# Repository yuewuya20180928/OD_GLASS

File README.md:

# OD_GLASS — ARS45 一体式智能眼镜

> **1 台样机** · ARS45 (12nm / 6 TOPS / 512MB) · MIPI-CSI 单路 sensor → NPU 跑 YOLOv5 INT8 80 类 → 800×600 显示 + JBD 走鹃Ⅱ + 衍射光波导一拖二双目
> 硬指标: **端到端 < 60ms** · **皮肤接触 ≤43°C** · **续航 ≥1h (按需触发)**

本仓库记录项目的**全部工程信息 + 4-Agent 协同开发体系**。
最新快照: `docs/PROJECT_STATUS.md` · 决策: `docs/DECISIONS.md` · 未闭环问题: `docs/OPEN_ISSUES.md`

---

## 0. ★ 从这里开始 → [`docs/START_HERE.md`](docs/START_HERE.md)

> 30 秒知道: 现在在哪个阶段 / 这一阶段要什么 / 正在跑什么 / 下一步 3 件事 / 哪些数字不能信

## 0. 这不是一个人的项目 —— 是 4 个 Agent 的协同产物

```
                      ┌─────────────────────────┐
                      │  main = 项目总工 (moli) │
                      │  方案/选型/拆解/计划/   │
                      │  收口/质量与进度把控     │
                      └───────────┬─────────────┘
        ┌─────────────────────────┼─────────────────────────┐
        │                         │                         │
┌───────▼────────┐      ┌─────────▼────────┐      ┌─────────▼────────┐
│  hw-lead       │      │  sw-lead         │      │  mech-lead      │
│  硬件总工      │      │  软件总工        │      │  结构总工(散热) │
│  原理图/PCB    │      │  需求拆解/方案   │      │  空间预算/散热  │
│  拆解/审核     │      │  开发与验证      │      │  打印件实现     │
└────────────────┘      └──────────────────┘      └──────────────────┘
        ↑                        ↑                        ↑
        └──────── 走共享状态源 STATE.yaml + HANDOFF 交接单 ────┘
              ★ 三个子总工之间【不做直接沟通】(星型拓扑, 硬规则)
```

**为什么这么设计**: 项目总工的核心职责是"需求对接 + 跨模块串联", 而它已经持有全部项目上下文; 另建一个总工等于把上下文切一半出去还多一跳中转。三个子总工之间**横向信息流走文件, 不走对话** —— 堵死的是"对话"不是"信息", 否则结构总工看不到硬件的 PCB 尺寸, 各写各的。

→ 完整说明: **[`docs/AGENT_SYSTEM.md`](docs/AGENT_SYSTEM.md)**

---

## 0.4 当前进展与待办 (一页看懂) → [`docs/STATUS_SUMMARY.md`](docs/STATUS_SUMMARY.md)
> 2026-10-26 19:45 更新: 一天内闭环 8 件 (打印包 Rev A / ISP 整幅 scale / 功耗 V2 / 电池容量口径 / 可靠性 / 原理图 V1 启动 / 网上查证 / 工程基建), 未闭环 41 条, 3 个硬指标的真实状态与杠杆, 待办分 5 桶, 风险 Top 3。

## 0.5 接下来干什么 → [`docs/TODO.md`](docs/TODO.md)

```
A 桶 立刻可派 (内部, 不等任何人)   14 条   → 三个总工的活, 随时能派
B 桶 等你拍板 (回一句就解锁)         3 条   → 3 份外发草稿 + 测试设备预算
C 桶 等外部 (原厂 9 / JBD 3)        13 条   → 不是谁的锅, 但有 due 与升级点
D 桶 依赖关系                              → 草稿发出 → G1; 打印环境 → G2; 测试设备 → G3
```

---

## 1. 当前状态 (自动生成, 数字与真源一致)

> ★**本 README 不含任何会过期的数字** —— 状态一律看下面这几份**自动生成**的文档:

| 文档 | 内容 |
|---|---|
| **[`docs/START_HERE.md`](docs/START_HERE.md)** | ★**接手指南: 30 秒现状 / 下一步 3 件事 / 正在跑 / 等你拍板 / 哪些数字不能信** |
| [`docs/STATUS_SUMMARY.md`](docs/STATUS_SUMMARY.md) | 一页看懂 (现状 / 闭环了什么 / 三个硬指标真状态 / 待办分桶 / 风险 Top3) |
| [`docs/PROJECT_STATUS.md`](docs/PROJECT_STATUS.md) | 8 节状态快照 (质量门 / 阶段门 / 就绪度 / 配置审计 / 决策账) |
| [`docs/OPEN_ISSUES.md`](docs/OPEN_ISSUES.md) | 问题清单 (按责任方分桶 + 未闭环明细 + 已关闭台账) |
| [`docs/TODO.md`](docs/TODO.md) | 接下来干什么 (在飞 / 可派 / 等你 / 等外部 / 依赖关系 / 复现命令) |

## 2. 目录

```
docs/
  TODO.md                 ★★ **接下来干什么** (按"能不能真动"分 4 桶: 立刻可派 / 等你拍板 / 等外部 / 依赖关系) —— 先看这份
  AGENT_SYSTEM.md          ★ 4 个 Agent 的职责/边界/配置/通信规则/质量门 (核心)
  PROJECT_STATUS.md          当前状态快照 (自动生成)
  DECISIONS.md               决策日志 (老板拍板原话 + 推导)
  OPEN_ISSUES.md             未闭环问题清单 (自动生成)
  FRAMEWORK_SCOPE.md         框架裁剪基线表 (9 域 68 项 + 6 项专属, 逐条裁剪)
  DECISION_TABLE_Q1_Q4_Q17.md  端到端/续航/帧率 三件决策表
  CERT_CHECKLIST.md          认证清单 (仅国内)
  STRESS_TEST_2026-10-25.md  Agent 通信压测报告 (抓到 11 个缺陷)
  INTERFACES.md              跨模块接口契约
  PRINT_SETUP.md             打印执行卡 (P2S 切片参数 + 41 项测量)
config/
  openclaw.agents.json     ★ 脱敏后的 4-Agent 配置 (凭据已剔除)
  agents/{main,hw-lead,sw-lead,mech-lead}/AGENTS.md
                           ★ 四个角色的岗位说明书 (职责/边界/交付标准)
projects/smart_glasses/    完整项目库 (真源)
  PROJECT_TRACKER.md         ★ 唯一真源 (35+ 条锁死变量 + 全部章节)
  state/                     状态源协议 + 11 个质量门/巡检脚本 (可复现)
  HW/ SW/ MECH/ REQ/ HANDOFF/ PRINT/  三个总工的产出区
  FRAMEWORK/                 ★ 框架层文档 (项目总工产出)
    ARCH_DIAGRAM.md            系统架构 / 信号流 / 数据流
    STACKUP.md                 尺寸堆叠 (镜脚/镜框/镜头)
    POWER_TREE.md              电源拓扑 + 热账 + 散热三件套
    INTERFACE_SPEC.md          ★ 接口规格书 (电气/机械/热/软件四层)
    RISK_REGISTER.md           ★ 风险登记册 (21 风险 + 应急备选 + 复查节奏)
    RTM.md                     ★ 需求→设计→验证 追溯矩阵
    CHANGE_LOG.md              ★ 规格变更追踪 (含 10 条已作废结论)
    EXTERNAL_PARTIES.md        ★ 外部方管理 (含"未回时的备份方案")
    QCP.md                     来料检验 + 整机测试项
    AFTERSALES.md              售后诊断 + 返修流程
    FRAMEWORK_SCOPE.md         9 域 68 项逐条裁剪基线
```

---

## 3. 怎么跑 (全部可复现, 不需要额外环境)

```bash
cd projects/smart_glasses

./status.sh                    # 一屏: 进展/待办(按责任方分 5 桶)/卡点/风险
python3 state/advance.py       # 下一批可执行动作 (--apply 落盘派活)
python3 state/issue_check.py   # 问题闭环门 (字段/状态机/验证分离/逾期/双向覆盖)
python3 state/stage_gate.py    # 阶段门: 现在在第几关, 缺什么
python3 state/readiness.py     # 执行就绪度 (组织与机制, 38 条判据)
python3 state/agent_config_check.py   # Agent 配置审计 (81 条判据, 能否开工)
python3 state/daily_check.py   # 每日巡检 + 漂移检测
python3 state/merge.py         # 状态源合并 (rc 0=完整 2=不完整 1=崩)
```

---

## 4. 三条最该记住的教训

**① 数字不能自己估** — 我给决策表写"0.23W → 皮肤 38-40°C ✅", 结构总工重算是 **46.5°C ❌ 仍超 43°C 红线**, 还漏了整个充电场景 (0.8W → 75.1°C)。
→ *给用户的数必须引子总工的核算原文。*

**② 验收分离: 自己修的必须别人验** — 问题的 `verify_by ≠ owner` 是硬门禁, 自己修自己验等于没验。三个子总工因此抓到总工的三处错 (温度数 / Q17 切换判据 / 验证人填自己)。

**③ 阶段性结论要标证据等级** — `[实测] / [官方] / [推算] / [0数据]`。本项目**至今零实测**, 所有数字都是推算; 推算值不能冒充实测, 阶段门只认 `kind == "实测"`。

---

## 5. 现状一句话

> **纸面阶段已做到滴水不漏, 但一个实测数都没有。**
> 阶段门 G0 → G1 (原理图/PCB 定稿) 差 4 项; 三个硬指标 (端到端 60ms / 皮肤 43°C / 续航 1h) 目前**全是推算**,
> 达标结论必须等投板后的实测。
> → **当前目标 / 计划 / 下一步 / 正在跑 / 等你拍板: 见 [`docs/START_HERE.md`](docs/START_HERE.md)** (自动生成, 数字不过期)
> → **唯一真源**: `projects/smart_glasses/PROJECT_TRACKER.md` (有章节地图)

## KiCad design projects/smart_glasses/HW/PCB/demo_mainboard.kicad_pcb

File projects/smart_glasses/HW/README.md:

# HW/ — 硬件总工 hw-lead 的产出区

规则:
- 只放**本角色**的交付物, 文件名带日期/版本 (例: `2025-10-25_schematic_v1.pdf`)
- 大文件 (PDF / PCB / 3D / 固件) 放这里, 聊天里只发绝对路径
- 需求变更先写交接单到 `../HANDOFF/`, 不要直接改 `../PROJECT_TRACKER.md`

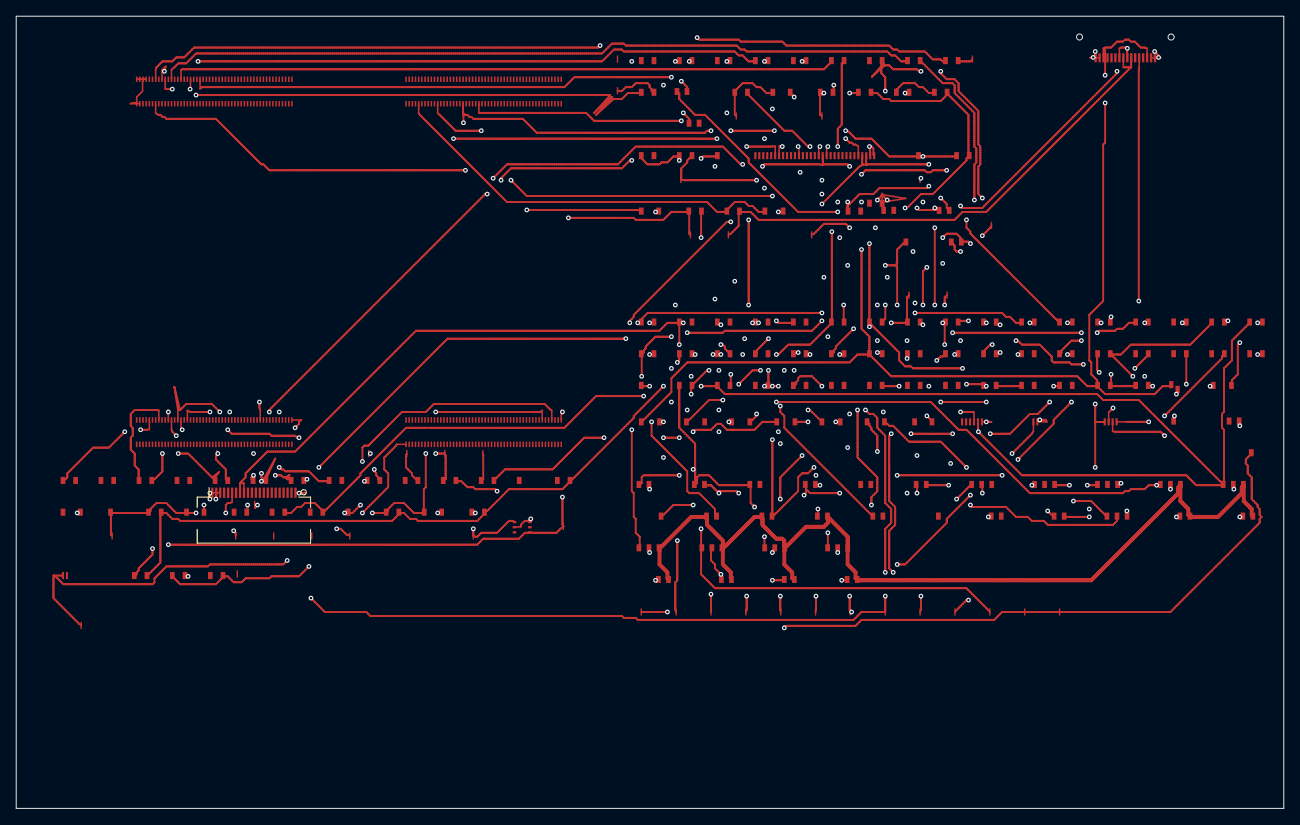
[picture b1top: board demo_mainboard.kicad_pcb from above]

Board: 8 copper layers, 160.0 x 100.0 mm, 186 parts (0 on the bottom side), 115 nets.

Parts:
BT_432243: 432243 3.7V ≥420mAh
CHG_GND_STAR: 单点汇流位
CONN_CAM: GND
CONN_LIGHT: HIROSE FH12-22S-0.5SH(55) 22p 0.5mm
C_AC_CSI_D0_CK_N, C_AC_CSI_D0_CK_P, C_AC_CSI_D0_D0_N, C_AC_CSI_D0_D0_P, C_AC_CSI_D0_D1_N, C_AC_CSI_D0_D1_P, C_AC_CSI_D0_D2_N, C_AC_CSI_D0_D2_P, C_AC_CSI_D0_D3_N, C_AC_CSI_D0_D3_P: 100nF ±10%
C_BULK_LIGHT_1V8, C_BULK_LIGHT_3V3: 10µF
C_BULK_SENSOR_AVDD: 10µF
C_BULK_SENSOR_CORE: 10µF
C_BULK_SENSOR_VDD_IO: 10µF
C_BULK_VDD_1V8_IO, C_BULK_VDD_3V3_IO: 10µF
C_BULK_V_CORE: 10µF
C_BULK_V_SOC_IO: 10µF
C_DET_BAT: 100nF ±10%
C_DET_VBUS_D: 100nF ±10%
C_HF_LIGHT_1V8, C_HF_LIGHT_3V3: 100nF
C_HF_SENSOR_AVDD: 100nF
C_HF_SENSOR_CORE: 100nF
C_HF_SENSOR_VDD_IO: 100nF
C_HF_VDD_1V8_IO, C_HF_VDD_3V3_IO: 100nF
C_HF_V_CORE: 100nF
C_HF_V_SOC_IO: 100nF
C_KEY_CAM: 100nF ±10%
C_KEY_PWR: 100nF ±10%
C_KEY_VM: 100nF ±10%
C_KEY_VP: 100nF ±10%
C_RST: 100nF ±10%
C_SUPV: 100nF ±10%
C_SW_IN: 10µF ±20%
C_SW_OUT: 10µF ±20%
C_TEMP: 100nF ±10%
C_VBUS_DEMO: 10µF ±20%
C_VBUS_GND: [待选型] 100µF
C_XTAL_IN: 12pF ±10%
C_XTAL_OUT: 12pF ±10%
D_ESD_CAM: ESD 阵列 [待选型]
D_ESD_DEMO: ESD 阵列 [待选型] (USB 2.0)
D_ESD_LIGHT: ESD 阵列 [待选型]
D_ESD_USB_D: ESD 阵列 [待选型] (USB 2.0 双通道)
D_LED_B: LED (待选型)
D_LED_G: LED (待选型)
D_LED_R: LED (待选型)
FB_DEMO: π 滤波磁珠 [待选型]
J_BOOT1: 启动存储焊盘位 (4p 信号 + 2p 电源/GND 预留)
J_CHG: SoM BTB CHG (100pin, 部分已分配)
J_DEBUG: 1×4 1.27mm 排针 (JTAG)
J_SOM_P1: Hirose DF40C-100DS-0.4V(51) 100pin 0.4mm (SOM P1)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
J_SOM_P2: Hirose DF40C-100DS-0.4V(51) 100pin 0.4mm (SOM P2)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
J_SOM_P3: Hirose DF40C-100DS-0.4V(51) 100pin 0.4mm (SOM P3)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
J_SOM_P4: Hirose DF40C-100DS-0.4V(51) 100pin 0.4mm (SOM P4)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
J_UART: 1×2 1.27mm 排针 (UART)
J_USB_C: GCT USB4105-16P USB-C 电源口 (自绘, 原厂图纸 Rev B3)
Q1, Q2: [待选型] N-MOS
Q_AND: [待选型] N-MOS (硬件 AND)
Q_ENVC: [待选型] N-MOS (反相)
Q_PG: [待选型] **P-MOS 高边开关** (低漏, Vgs(th) 明确)
R_BAT_DET_1, R_BAT_DET_2: 1M ±1%
R_CC1_D: 5.1k ±1% (CC1 下拉)
R_CC2_D: 5.1k ±1% (CC2 下拉)
R_EN_VCORE: 10k ±1%
R_ID_JMP0, R_ID_JMP1: 0Ω (跳线位)
R_JTAG_TCK: 100Ω ±1%
R_JTAG_TDI: 100Ω ±1%
R_JTAG_TDO: 100Ω ±1%
R_JTAG_TMS: 100Ω ±1%
R_KEY_CAM: 10k ±1%
R_KEY_PWR: 10k ±1%
R_KEY_VM: 10k ±1%
R_KEY_VP: 10k ±1%
R_LED_B: 1k ±1%
R_LED_G: 1k ±1%
R_LED_R: 1k ±1%
R_NTC_BAT: 103AT NTC ±1% (贴电芯, 另一端接 TS 专用回流)
R_PD_ON: 10k ±1%
R_PG_PULL: 10k ±1%
R_PU_BOOT_N: 10k ±1%
R_PU_I2CA_SCL, R_PU_I2CA_SDA: 2.2k ±1%
R_PU_I2CB_SCL, R_PU_I2CB_SDA: 4.7k ±1%
R_PU_ID0, R_PU_ID1: 10k ±1%
R_PU_PG: 10k ±1%
R_PU_RESET_N: 10k ±1%
R_SEL_CK_N: 0Ω
R_SEL_CK_P: 0Ω
R_SEL_D0_N, R_SEL_D0_P, R_SEL_D1_N, R_SEL_D1_P, R_SEL_D2_N, R_SEL_D2_P, R_SEL_D3_N, R_SEL_D3_P: 0Ω
R_SER_CSI_MCLK: [待原厂]
R_SER_FSIN: 50Ω ±1%
R_SER_RESET_N: 1k ±1%
R_SER_SPI_CSn: 0Ω (串阻位)
R_SER_SPI_MISO: 0Ω (串阻位)
R_SER_SPI_MOSI: 0Ω (串阻位)
R_SER_SPI_SCLK: 0Ω (串阻位)
R_SER_USB_D_N: 22Ω ±1%
R_SER_USB_D_P: 22Ω ±1%
R_SUPV_DIV1: [待选型] 分压上臂 (0Ω 跳线位)
R_SUPV_DIV2: [待选型] 分压下臂 (0Ω 跳线位)
R_TS_PULL: 30.31k ±1%
R_VBUS_DET_D1: 1M ±1% (上臂)
R_VBUS_DET_D2: 1M ±1% (下臂)
SW_BOOT: BOOT 按键 (待选型)
SW_KEY_CAM: 按键 (待选型)
SW_KEY_PWR: 按键 (待选型)
SW_KEY_VM: 按键 (待选型)
SW_KEY_VP: 按键 (待选型)
SW_RST: 复位按键 (待选型)
TP_BAT: 测试点
TP_BAT_CHG: 跨铰链段压降测点
TP_BOOT: 测试点
TP_CSI_CK_N: 测试点
TP_CSI_CK_P: 测试点
TP_CSI_D0_N, TP_CSI_D0_P: 测试点
TP_DSI_CK_N: 测试点
TP_DSI_CK_P: 测试点
TP_DSI_D0_N, TP_DSI_D0_P, TP_DSI_D1_N, TP_DSI_D1_P, TP_DSI_D2_N, TP_DSI_D2_P, TP_DSI_D3_N, TP_DSI_D3_P: 测试点
TP_FSIN: 测试点
TP_I2CA_SCL, TP_I2CA_SDA, TP_I2CB_SCL, TP_I2CB_SDA: 测试点
TP_ID: 测试点
TP_JTAG: 测试点
TP_KEY_PWR: 测试点
TP_KEY_VM: 测试点
TP_KEY_VP: 测试点
TP_LED_B: 测试点
TP_LED_G: 测试点
TP_LED_R: 测试点
TP_LIGHT_3V3: 测试点
TP_MCLK: 测试点
TP_PG: 测试点
TP_PG_VCORE: PG (开漏, 需上拉)
TP_PG_VIO: PG (开漏, 需上拉)
TP_RESET: 测试点
TP_SYS: 测试点
TP_UART: 测试点
TP_USB_D_N: 测试点
TP_USB_D_P: 测试点
TP_VCORE: 测试点
TP_VIO: 测试点
U_BATPROT: BQ2970
U_DCDC_VCORE: EN 输入 (高 = 使能)
U_DCDC_VIO: EN 输入 (高 = 使能)
U_EN_SW: EN 输入 (高=放行底板)
U_LDO_IO18, U_LDO_IO33: EN (pin3)
U_LDO_L18, U_LDO_L33: EN (pin3)
U_LDO_S12, U_LDO_S18B: EN (pin3)
U_LDO_S28: GND (pin2)
U_PWR_SW: VIN (输入)
U_SUPV: CT 脚 (阈值/延时选择)
U_TEMP: TI TMP117 (WSON-6 DRV0006B, 2x2mm)
X1: 晶振焊盘位 (不装)

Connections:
BAT: R_BAT_DET_1.2, TP_BAT.1, U_BATPROT.4
BAT_CELL_N: BT_432243.2, U_BATPROT.6
BAT_CELL_P: BT_432243.1, Q1.3
BAT_CHG: J_CHG.1, TP_BAT_CHG.1
BAT_COUT: Q2.5, U_BATPROT.2
BAT_DET: C_DET_BAT.1, J_SOM_P1.38, R_BAT_DET_1.1, R_BAT_DET_2.1
BAT_DOUT: Q1.5, U_BATPROT.3
BAT_GATE: Q1.2, Q2.2
BAT_PROT_CELL: Q1.4, Q2.3
BAT_PROT_CELL2: Q2.4, U_BATPROT.5
BAT_SW: C_SW_IN.1, Q_PG.2, U_BATPROT.7, U_PWR_SW.1
BOOT_N: J_SOM_P1.28, R_PU_BOOT_N.1, SW_BOOT.1, TP_BOOT.1
CAM_RESET_N: CONN_CAM.27, J_SOM_P1.54
CARRIER_BOARD_EN: J_SOM_P3.87, U_EN_SW.2
CSI_D0_CK_N: CONN_CAM.17, C_AC_CSI_D0_CK_N.2, TP_CSI_CK_N.1
CSI_D0_CK_N_SRC: C_AC_CSI_D0_CK_N.1, J_SOM_P4.77
CSI_D0_CK_P: CONN_CAM.18, C_AC_CSI_D0_CK_P.2, D_ESD_CAM.2, TP_CSI_CK_P.1
CSI_D0_CK_P_SRC: C_AC_CSI_D0_CK_P.1, J_SOM_P4.79
CSI_D0_D0_N: CONN_CAM.14, C_AC_CSI_D0_D0_N.2, TP_CSI_D0_N.1
CSI_D0_D0_N_SRC: C_AC_CSI_D0_D0_N.1, J_SOM_P4.65
CSI_D0_D0_P: CONN_CAM.15, C_AC_CSI_D0_D0_P.2, TP_CSI_D0_P.1
CSI_D0_D0_P_SRC: C_AC_CSI_D0_D0_P.1, J_SOM_P4.67
CSI_D0_D1_N: CONN_CAM.11, C_AC_CSI_D0_D1_N.2
CSI_D0_D1_N_SRC: C_AC_CSI_D0_D1_N.1, J_SOM_P4.71
CSI_D0_D1_P: CONN_CAM.12, C_AC_CSI_D0_D1_P.2
CSI_D0_D1_P_SRC: C_AC_CSI_D0_D1_P.1, J_SOM_P4.73
CSI_D0_D2_N: CONN_CAM.5, C_AC_CSI_D0_D2_N.2
CSI_D0_D2_N_SRC: C_AC_CSI_D0_D2_N.1, J_SOM_P4.83
CSI_D0_D2_P: CONN_CAM.6, C_AC_CSI_D0_D2_P.2
CSI_D0_D2_P_SRC: C_AC_CSI_D0_D2_P.1, J_SOM_P4.85
CSI_D0_D3_N: CONN_CAM.2, C_AC_CSI_D0_D3_N.2
CSI_D0_D3_N_SRC: C_AC_CSI_D0_D3_N.1, J_SOM_P4.89
CSI_D0_D3_P: CONN_CAM.3, C_AC_CSI_D0_D3_P.2
CSI_D0_D3_P_SRC: C_AC_CSI_D0_D3_P.1, J_SOM_P4.91
CSI_MCLK: CONN_CAM.20, R_SER_CSI_MCLK.2, TP_MCLK.1
CSI_MCLK_SRC: J_SOM_P2.45, R_SER_CSI_MCLK.1
DSI_D0_CK_N: CONN_LIGHT.5, R_SEL_CK_N.2, TP_DSI_CK_N.1
DSI_D0_CK_N_SRC: J_SOM_P3.69, R_SEL_CK_N.1
DSI_D0_CK_P: CONN_LIGHT.6, R_SEL_CK_P.2, TP_DSI_CK_P.1
DSI_D0_CK_P_SRC: J_SOM_P3.71, R_SEL_CK_P.1
DSI_D0_D0_N: CONN_LIGHT.8, R_SEL_D0_N.2, TP_DSI_D0_N.1
DSI_D0_D0_N_SRC: J_SOM_P3.57, R_SEL_D0_N.1
DSI_D0_D0_P: CONN_LIGHT.9, R_SEL_D0_P.2, TP_DSI_D0_P.1
DSI_D0_D0_P_SRC: J_SOM_P3.59, R_SEL_D0_P.1
DSI_D0_D1_N: CONN_LIGHT.2, R_SEL_D1_N.2, TP_DSI_D1_N.1
DSI_D0_D1_N_SRC: J_SOM_P3.63, R_SEL_D1_N.1
DSI_D0_D1_P: CONN_LIGHT.3, R_SEL_D1_P.2, TP_DSI_D1_P.1
DSI_D0_D1_P_SRC: J_SOM_P3.65, R_SEL_D1_P.1
DSI_D0_D2_N: CONN_LIGHT.16, R_SEL_D2_N.2, TP_DSI_D2_N.1
DSI_D0_D2_N_SRC: J_SOM_P3.75, R_SEL_D2_N.1
DSI_D0_D2_P: CONN_LIGHT.17, R_SEL_D2_P.2, TP_DSI_D2_P.1
DSI_D0_D2_P_SRC: J_SOM_P3.77, R_SEL_D2_P.1
DSI_D0_D3_N: CONN_LIGHT.18, R_SEL_D3_N.2, TP_DSI_D3_N.1
DSI_D0_D3_N_SRC: J_SOM_P3.81, R_SEL_D3_N.1
DSI_D0_D3_P: CONN_LIGHT.19, R_SEL_D3_P.2, TP_DSI_D3_P.1
DSI_D0_D3_P_SRC: J_SOM_P3.83, R_SEL_D3_P.1
EN_VCORE: Q_ENVC.3, R_EN_VCORE.1, U_DCDC_VCORE.13
FSIN_OUT: R_SER_FSIN.1, TP_FSIN.1
GND: CHG_GND_STAR.1, CONN_CAM.1, CONN_CAM.4, CONN_CAM.7, CONN_CAM.10, CONN_CAM.13, CONN_CAM.16, CONN_CAM.19, CONN_CAM.21, CONN_LIGHT.1, CONN_LIGHT.4, CONN_LIGHT.7, CONN_LIGHT.10, CONN_LIGHT.13, CONN_LIGHT.20, CONN_LIGHT.21, CONN_LIGHT.22, C_BULK_LIGHT_1V8.2, C_BULK_LIGHT_3V3.2, C_BULK_SENSOR_AVDD.2, C_BULK_SENSOR_CORE.2, C_BULK_SENSOR_VDD_IO.2, C_BULK_VDD_1V8_IO.2, C_BULK_VDD_3V3_IO.2, C_BULK_V_CORE.2, C_BULK_V_SOC_IO.2, C_DET_BAT.2, C_DET_VBUS_D.1, C_HF_LIGHT_1V8.2, C_HF_LIGHT_3V3.2, C_HF_SENSOR_AVDD.2, C_HF_SENSOR_CORE.2, C_HF_SENSOR_VDD_IO.2, C_HF_VDD_1V8_IO.2, C_HF_VDD_3V3_IO.2, C_HF_V_CORE.2, C_HF_V_SOC_IO.2, C_RST.2, C_SUPV.2, C_SW_IN.2, C_SW_OUT.2, C_TEMP.2, C_VBUS_DEMO.2, C_VBUS_GND.1, C_XTAL_IN.2, C_XTAL_OUT.2, D_ESD_CAM.1, D_ESD_DEMO.2, D_ESD_LIGHT.2, D_ESD_USB_D.2, D_LED_B.2, D_LED_G.2, D_LED_R.2, FB_DEMO.2, J_BOOT1.6, J_USB_C.A1, J_USB_C.A12, J_USB_C.B1, J_USB_C.B12, Q1.6, Q2.6, Q_AND.2, Q_ENVC.2, R_CC1_D.1, R_CC2_D.2, R_ID_JMP0.2, R_ID_JMP1.2, R_PD_ON.2, R_SUPV_DIV2.2, R_VBUS_DET_D2.2, SW_BOOT.2, SW_KEY_CAM.2, SW_KEY_PWR.2, SW_KEY_VM.2, SW_KEY_VP.2, SW_RST.2, U_EN_SW.4, U_LDO_IO18.2, U_LDO_IO18.5, U_LDO_IO33.2, U_LDO_IO33.5, U_LDO_L18.2, U_LDO_L18.5, U_LDO_L33.2, U_LDO_L33.5, U_LDO_S12.2, U_LDO_S12.5, U_LDO_S18B.2, U_LDO_S18B.5, U_LDO_S28.2, U_LDO_S28.5, U_PWR_SW.4, U_TEMP.2, U_TEMP.4
I2C_A_SCL: CONN_CAM.24, J_SOM_P2.31, R_PU_I2CA_SCL.1, TP_I2CA_SCL.1
I2C_A_SDA: CONN_CAM.25, J_SOM_P2.33, R_PU_I2CA_SDA.1, TP_I2CA_SDA.1
I2C_B_SCL: CONN_LIGHT.11, J_SOM_P2.11, R_PU_I2CB_SCL.1, TP_I2CB_SCL.1, U_TEMP.1
I2C_B_SDA: CONN_LIGHT.12, J_SOM_P2.1, R_PU_I2CB_SDA.1, TP_I2CB_SDA.1, U_TEMP.6
ID_DETECT_0: J_SOM_P1.32, R_ID_JMP0.1, R_PU_ID0.1, TP_ID.1
ID_DETECT_1: J_SOM_P1.36, R_ID_JMP1.1, R_PU_ID1.1
JTAG_TCK: J_DEBUG.1, R_JTAG_TCK.2, TP_JTAG.1
JTAG_TDI: J_DEBUG.3, R_JTAG_TDI.2
JTAG_TDO: J_DEBUG.4, R_JTAG_TDO.2
JTAG_TMS: J_DEBUG.2, R_JTAG_TMS.2
KEY_CAM: C_KEY_CAM.1, J_SOM_P4.3, R_KEY_CAM.1, SW_KEY_CAM.1
KEY_PWR: C_KEY_PWR.1, J_SOM_P1.64, R_KEY_PWR.1, SW_KEY_PWR.1, TP_KEY_PWR.1
KEY_VOL_M: C_KEY_VM.1, J_SOM_P4.1, R_KEY_VM.1, SW_KEY_VM.1, TP_KEY_VM.1
KEY_VOL_P: C_KEY_VP.1, J_SOM_P2.13, R_KEY_VP.1, SW_KEY_VP.1, TP_KEY_VP.1
LED_B: J_SOM_P4.21, R_LED_B.1, TP_LED_B.1
LED_B_D: D_LED_B.1, R_LED_B.2
LED_G: J_SOM_P4.19, R_LED_G.1, TP_LED_G.1
LED_G_D: D_LED_G.1, R_LED_G.2
LED_R: J_SOM_P1.80, R_LED_R.1, TP_LED_R.1
LED_R_D: D_LED_R.1, R_LED_R.2
LIGHT_1V8: C_BULK_LIGHT_1V8.1, C_HF_LIGHT_1V8.1, U_LDO_L18.1
LIGHT_3V3: CONN_CAM.28, CONN_CAM.29, CONN_LIGHT.14, CONN_LIGHT.15, C_BULK_LIGHT_3V3.1, C_HF_LIGHT_3V3.1, TP_LIGHT_3V3.1, U_LDO_L33.1
LIGHT_5V: CONN_CAM.30, CONN_CAM.31, D_ESD_LIGHT.1
NET_USB_D_N_TYPEC: J_USB_C.A7, J_USB_C.B7, R_SER_USB_D_N.2, TP_USB_D_N.1
NET_USB_D_P_TYPEC: J_USB_C.A6, J_USB_C.B6, R_SER_USB_D_P.2, TP_USB_D_P.1
PG_AND: Q_AND.3, Q_ENVC.1, R_PG_PULL.1, TP_PG_VCORE.1, TP_PG_VIO.1, U_DCDC_VCORE.4, U_DCDC_VIO.4
PWR_GOOD: J_CHG.6, Q_PG.3, R_PU_PG.2, TP_PG.1
PWR_ON: J_SOM_P3.88, Q_PG.1, R_PD_ON.1, U_PWR_SW.2
RAIL_DEMO_5V: C_VBUS_DEMO.1, D_ESD_DEMO.1, FB_DEMO.1, J_USB_C.A4, J_USB_C.A9, J_USB_C.B4, J_USB_C.B9, R_VBUS_DET_D1.1, U_EN_SW.1
RAIL_SOM_DCIN: J_SOM_P3.91, J_SOM_P3.93, J_SOM_P3.95, J_SOM_P3.97, J_SOM_P3.98, J_SOM_P3.99, J_SOM_P3.100
RESET_N: Q_AND.1, R_PU_RESET_N.1, R_SER_RESET_N.1, SW_RST.1, TP_RESET.1, U_SUPV.1
RESET_N_SOC: C_RST.1, J_SOM_P2.100, R_SER_RESET_N.2
SENSOR_AVDD: C_BULK_SENSOR_AVDD.1, C_HF_SENSOR_AVDD.1, U_LDO_S28.1
SENSOR_CORE: C_BULK_SENSOR_CORE.1, C_HF_SENSOR_CORE.1, U_LDO_S12.1
SENSOR_VDD_IO: C_BULK_SENSOR_VDD_IO.1, C_HF_SENSOR_VDD_IO.1, U_LDO_S18B.1
SPI_CSn_BOOT: J_BOOT1.2, R_SER_SPI_CSn.2
SPI_MISO_BOOT: J_BOOT1.4, R_SER_SPI_MISO.2
SPI_MOSI_BOOT: J_BOOT1.3, R_SER_SPI_MOSI.2
SPI_SCLK_BOOT: J_BOOT1.1, R_SER_SPI_SCLK.2
SUPV_SENSE: R_SUPV_DIV1.2, R_SUPV_DIV2.1, U_SUPV.5
SYS: C_SW_OUT.1, TP_SYS.1, U_PWR_SW.3
SYS_PCB: U_DCDC_VCORE.15, U_DCDC_VIO.15, U_LDO_IO18.3, U_LDO_IO18.4, U_LDO_IO33.3, U_LDO_IO33.4, U_LDO_L18.3, U_LDO_L18.4, U_LDO_L33.3, U_LDO_L33.4, U_LDO_S12.3, U_LDO_S12.4, U_LDO_S18B.3, U_LDO_S18B.4, U_LDO_S28.4
TS_BAT: R_NTC_BAT.1, R_TS_PULL.1
UART_RX: J_SOM_P2.9, J_UART.2
UART_TX: J_SOM_P2.7, J_UART.1, TP_UART.1
USB_CC1: J_USB_C.A5, R_CC1_D.2
USB_CC2: J_USB_C.B5, R_CC2_D.1
USB_D_N_SRC: J_SOM_P1.94, R_SER_USB_D_N.1
USB_D_P_SRC: D_ESD_USB_D.1, J_SOM_P1.92, R_SER_USB_D_P.1
VBUS_DET_D: C_DET_VBUS_D.2, R_VBUS_DET_D1.2, R_VBUS_DET_D2.1
VDD_1V8_IO: C_BULK_VDD_1V8_IO.1, C_HF_VDD_1V8_IO.1, C_SUPV.1, R_EN_VCORE.2, R_PG_PULL.2, R_PU_BOOT_N.2, R_PU_I2CA_SCL.2, R_PU_I2CA_SDA.2, R_PU_RESET_N.2, U_LDO_IO18.1, U_SUPV.6
VDD_3V3_IO: C_BULK_VDD_3V3_IO.1, C_HF_VDD_3V3_IO.1, C_TEMP.1, J_BOOT1.5, R_KEY_CAM.2, R_KEY_PWR.2, R_KEY_VM.2, R_KEY_VP.2, R_PU_I2CB_SCL.2, R_PU_I2CB_SDA.2, R_PU_ID0.2, R_PU_ID1.2, R_PU_PG.1, U_LDO_IO33.1, U_TEMP.5
V_CORE: C_BULK_V_CORE.1, C_HF_V_CORE.1, TP_VCORE.1, U_DCDC_VCORE.14
V_SOC_IO: C_BULK_V_SOC_IO.1, C_HF_V_SOC_IO.1, R_SUPV_DIV1.1, TP_VIO.1, U_DCDC_VIO.14
XTAL_IN: C_XTAL_IN.1, X1.1
XTAL_OUT: C_XTAL_OUT.1, X1.2

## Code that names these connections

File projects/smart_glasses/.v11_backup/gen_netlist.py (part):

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        "必装", "[推算]", "",
        "电源域: 目标 3.0-4.2V / 最大电流 0.55A (330mA×1.5 + 瞬态); **R-F1 裁决: SYS 下限抬到 3.5V**; "
        "SoC 侧球位号 TBD-01", "C-02")
    add("P1", "SYS", "RAIL_SYS", "J_CHG pin1", "NET_SYS_3V3", "单端", "NET",
        "必装", "[推算]", "",
        "[SYS] 充电板 → 主 PCB 的主供电 (唯一跨板电源); 走 J_CHG pin1", "C-02")
    add("P1", "SYS", "J_CHG", "J_CHG pin1", "J_CHG", "1×6 1.27mm 排线座 (充电板↔主 PCB)", "CONN",
        "必装", "[推算]", "",
        "[SYS] 充电板↔主 PCB 连接器: pin1=SYS, pin2=VBUS_DET, pin3=BAT_DET, pin4=CHG_STAT, "
        "pin5=PWR_GOOD, pin6=GND; 型号/间距待结构与板宽确认; ★pin 编号为**本版自拟** "
        "(充电板在镜框 / 主 PCB 在镜脚, 必然跨铰链)", "C-02")

    # ---- ★V1.1 补画 1: 电池 NTC 接 BQ25896 的 TS 脚 (硬件停充, 安全项, V1 漏画) ----
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            "[推算]", "", f"[{rail}] 高频去耦电容 地端", cid)

    # LIGHT_5V: 无独立 IC, 直接取 VBUS (规格 C-10 'VBUS 直供')
    add("P1", "LIGHT_5V", "RAIL_LIGHT_5V", "CONN_LIGHT pin29", "RAIL_LIGHT_5V", "5.0V", "RAIL",
        "DNP", "[推算]", "TBD-02",
        "电源域: 目标 [待 JBD] / 最大电流 50mA; 供电方式 [待 JBD] 确认 (VBUS 直供 或 升压); "
        "SoC 侧球位号 TBD-01", "C-10")
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    add("P2", "VDD_3V3_IO", "R_PU_I2CA_SDA", "RAIL_VDD_3V3_IO", "R_PU_I2CA_SDA", "4.7k ±1%",
        "R", "必装", "[推算]", "",
        "[VDD_3V3_IO] I2C_A 上拉", "B-02")
    add("P2", "I2C_A_SCL", "CONN_CAM pin13", "NET_I2C_A_SCL", "NET_I2C_A_SCL",
        "上拉 4.7k 到 3.3V (灌 702µA, t_r=2.38µs@100pF)", "NET", "必装", "[推算]", "",
        "[I2C_A_SCL] 附加节点 (同 net)", "B-01")
    add("P2", "I2C_A_SDA", "CONN_CAM pin14", "NET_I2C_A_SDA", "NET_I2C_A_SDA",
        "上拉 4.7k 到 3.3V", "NET", "必装", "[推算]", "",
        "[I2C_A_SDA] 附加节点 (同 net)", "B-02")
    # NTC / 温度检测位: 规格 B-01 把 "NTC" 挂在 I2C_A 上, 但没说是裸 NTC 分压还是数字温度计
    # ★V1.1 定型 (ISS-086): 规格 B-01 的 "NTC 挂 I2C" 只能是**数字温度计** (裸 NTC 是分压不是 I2C)
    add("P2", "I2C_A_SCL", "U_TEMP pin2", "NET_I2C_A_SCL", "U_TEMP",
        "TMP117 数字温度计 (I2C 地址 0x48, ±0.1°C max, 16bit)", "IC", "必装", "[官方]", "",
        "[I2C_A_SCL] ★V1.1 定型: 选 TI TMP117 [官方 ti.com/product/TMP117] (1.7-5.5V 供电, 5µA max, "
        "WSON-2 2×2mm); I2C_A 从设备地址 0x48, 与 sensor 0x36 / 桥接 0x50 / 充电 IC 0x12 / "
        "光机 0x72 都不冲突; 若原厂坚持裸 NTC, 改 ADC 分压位 (不换板)", "B-01")
    add("P2", "I2C_A_SDA", "U_TEMP pin1", "NET_I2C_A_SDA", "U_TEMP",
        "TMP117 数字温度计", "IC", "必装", "[官方]", "", "[I2C_A_SDA] TMP117 SDA", "B-01")
    add("P2", "VDD_3V3_IO", "U_TEMP pin3", "RAIL_VDD_3V3_IO", "U_TEMP",
        "TMP117 数字温度计", "IC", "必装", "[官方]", "", "[I2C_A_SCL] TMP117 供电 (3.3V, 5µA max)",
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
    # ---- 充电状态回读 (BQ25896 STAT / PG, 开漏) ----
    for cid, sig, pin, rpu in (("B-05", "CHG_STAT", "J_CHG pin4", "R_PU_CHG_STAT"),
                               ("B-06", "PWR_GOOD", "J_CHG pin5", "R_PU_PG")):
        conn_row(by_id, cid, "P2", sig, "U_CHG", rpu, f"NET_{sig}")
        add("P2", "VDD_3V3_IO", rpu, "RAIL_VDD_3V3_IO", rpu, "10k ±1%",
            "R", "必装", "[推算]", "",
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             "NET_I2C_B_SCL")
    conn_row(by_id, "B-04", "P4", "I2C_B_SDA", "SoC[TBD-01].I2C_B_SDA", "R_PU_I2CB_SDA",
             "NET_I2C_B_SDA")
    add("P4", "I2C_B_SCL", "CONN_LIGHT pin13", "NET_I2C_B_SCL", "NET_I2C_B_SCL",
        "上拉 4.7k, 放主板侧", "NET", "必装", "[推算]", "TBD-04",
        "[I2C_B_SCL] 附加节点 (同 net)", "B-03")
    add("P4", "I2C_B_SDA", "CONN_LIGHT pin14", "NET_I2C_B_SDA", "NET_I2C_B_SDA",
        "上拉 4.7k, 放主板侧", "NET", "必装", "[推算]", "TBD-04",
        "[I2C_B_SDA] 附加节点 (同 net)", "B-04")
    add("P4", "VDD_3V3_IO", "R_PU_I2CB_SCL", "RAIL_VDD_3V3_IO", "R_PU_I2CB_SCL", "4.7k ±1%",
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    # ---- MCLK (单端, 单独包地) ----
    conn_row(by_id, "A-11", "P5", "CSI_MCLK_SRC", "SoC[TBD-01].CSI_MCLK", "R_SER_CSI_MCLK",
             "NET_CSI_MCLK_SRC")
    add("P5", "CSI_MCLK", "R_SER_CSI_MCLK", "CONN_CAM pin11", "R_SER_CSI_MCLK", "[待原厂]",
        "R", "必装", "[待原厂]", "TBD-03",
        "[CSI_MCLK] MCLK 串阻位 (**位必留**: MCLK 是时钟输出, 串阻兼做源端匹配/阻尼); "
        "值随 TBD-03 的 MCLK 电平与速率定, 不写死")
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        "单端, 10k 上拉", "NET", "必装", "[待原厂]", "TBD-03",
        "[CSI_RESET_N] 附加节点 (同 net)", "A-12")
    # ---- sensor 三条电源轨 → 连接器 ----
    for rail, pin in (("SENSOR_AVDD", 15), ("SENSOR_VDD_IO", 16), ("SENSOR_CORE", 17)):
        add("P5", rail, f"RAIL_{rail}", f"CONN_CAM pin{pin}", f"NET_{rail}",
            by_id_cid_rail(spec, rail), "NET", "必装", "[官方]", "",
            f"[{rail}] sensor 供电 接 CONN_CAM pin{pin} (跨铰链, 走线与 MCLK 并行 ≤5mm, 间距 ≥3mm)")
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        "必装", "[推算]", "TBD-10",
        "[USB_D_N] USB 2.0 源端串阻 (D-, 主板侧); ★V1.1 修: 同上, 改接 CONN_USB pin2")
    # ---- Type-C CC (Rd 下拉; 接 PD 控制器时由控制器接管) ----
    conn_row(by_id, "B-23", "P6", "USB_CC1", "J_TYPE_C pin2", "R_CC1", "NET_USB_CC1")
    add("P6", "USB_CC2", "J_TYPE_C pin3", "R_CC2", "R_CC2", "5.1k ±1%", "R", "必装", "[推算]",
        "", "[USB_CC2] Type-C Rd (非 PD 时下拉; 接 PD 控制器时由控制器接管)")
    add("P6", "GND", "R_CC1", "GND", "R_CC1", "5.1k ±1%", "R", "必装", "[推算]", "",
        "Type-C Rd 下拉端")
    add("P6", "GND", "R_CC2", "GND", "R_CC2", "5.1k ±1%", "R", "必装", "[推算]", "",
        "Type-C Rd 下拉端")
    add("P6", "USB_CC2", "USB_CC2", "J_TYPE_C pin3", "NET_USB_CC2", "单端", "NET", "必装",
        "[推算]", "", "[USB_CC2] CC2 网节点 (同 net)", "B-23")
    # ---- Type-C 座 GND / 屏蔽 + 跨铰链预留 ----
    add("P6", "GND", "J_TYPE_C pin6", "GND", "J_TYPE_C", "Type-C 16p 座", "CONN", "必装",
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# 全部测试点 (规格 13 个逻辑 TP → 展开成 40 个物理测点)
TPS = [
    ("TP_VBUS", "VBUS_5V", "J_TYPE_C pin1", "Type-C 入口 5V", "Type-C 出口侧 ≤3mm", "必装"),
    ("TP_SYS", "SYS", "J_CHG pin1", "系统 3.7V 主轨", "电池保护后", "必装"),
    ("TP_BAT", "BAT", "U_BATPROT", "电池电压", "BQ25896 BAT 脚", "必装"),
    ("TP_VCORE", "V_CORE", "U_DCDC_VCORE", "SoC 核心轨", "DC-DC 输出", "必装"),
    ("TP_VIO", "V_SOC_IO", "U_DCDC_VIO", "SoC IO 轨", "DC-DC/LDO 输出", "必装"),
    ("TP_SENSOR_2V8", "SENSOR_AVDD", "CONN_CAM pin15", "sensor 三条轨",
     "LDO 输出 (规格合并名 TP_SENSOR_3V3/1V8/2V8)", "必装"),
    ("TP_SENSOR_1V8", "SENSOR_VDD_IO", "CONN_CAM pin16", "sensor 三条轨",
     "LDO 输出 (规格合并名 TP_SENSOR_3V3/1V8/2V8)", "必装"),
    ("TP_SENSOR_1V2", "SENSOR_CORE", "CONN_CAM pin17", "sensor 三条轨",
     "LDO 输出 (规格合并名 TP_SENSOR_3V3/1V8/2V8)", "必装"),
    ("TP_LIGHT_3V3", "LIGHT_3V3", "CONN_LIGHT pin27", "光机轨", "LDO 输出", "必装"),
    ("TP_LIGHT_1V8", "LIGHT_1V8", "CONN_LIGHT pin28", "光机 1.8V 轨 (待 JBD)",
     "LDO 输出 (待 JBD 确认后)", "DNP"),
    ("TP_CSI_CK_P", "CSI_D0_CK_P", "CONN_CAM pin1", "CSI 时钟差分 (示波器测眼图/摆幅)",
     "连接器出口 (规格合并名 TP_CSI_D0_CK_P / _N)", "必装"),
    ("TP_CSI_CK_N", "CSI_D0_CK_N", "CONN_CAM pin2", "CSI 时钟差分 (规格合并名 TP_CSI_D0_CK_P / _N)",
     "连接器出口", "必装"),
    ("TP_CSI_D0_P", "CSI_D0_D0_P", "CONN_CAM pin3", "CSI D0 数据差分", "连接器出口", "必装"),
    ("TP_CSI_D0_N", "CSI_D0_D0_N", "CONN_CAM pin4", "CSI D0 数据差分", "连接器出口", "必装"),
    ("TP_CSI_RST", "CSI_RESET_N", "CONN_CAM pin12", "CSI 复位 (10k 上拉点)", "连接器出口", "必装"),
    ("TP_MCLK", "CSI_MCLK", "CONN_CAM pin11", "MCLK (包地走线)", "连接器出口", "必装"),
    ("TP_DSI_CK_P", "DSI_D0_CK_P", "CONN_LIGHT pin3", "DSI 时钟差分",
     "连接器出口 (规格合并名 TP_DSI_D0_CK_P / _N)", "必装"),
    ("TP_DSI_CK_N", "DSI_D0_CK_N", "CONN_LIGHT pin4", "DSI 时钟差分 (规格合并名 TP_DSI_D0_CK_P / _N)",
     "连接器出口", "必装"),
    ("TP_DSI_D0_P", "DSI_D0_D0_P", "CONN_LIGHT pin5", "DSI D0 数据差分", "连接器出口", "必装"),
    ("TP_DSI_D0_N", "DSI_D0_D0_N", "CONN_LIGHT pin6", "DSI D0 数据差分", "连接器出口", "必装"),
    ("TP_I2CA_SCL", "I2C_A_SCL", "CONN_CAM pin13", "I2C_A 时钟", "连接器出口", "必装"),
    ("TP_I2CA_SDA", "I2C_A_SDA", "CONN_CAM pin14", "I2C_A 数据", "连接器出口", "必装"),
    ("TP_I2CB_SCL", "I2C_B_SCL", "CONN_LIGHT pin13", "DDC 时钟 (I2C_B)", "连接器出口", "必装"),
    ("TP_I2CB_SDA", "I2C_B_SDA", "CONN_LIGHT pin14", "DDC 数据 (I2C_B)", "连接器出口", "必装"),
    ("TP_USB_D_P", "USB_D_P", "CONN_USB pin1", "USB 2.0 差分",
     "Type-C 出口 (规格合并名 TP_USB_D+ / D-)", "必装"),
    ("TP_USB_D_N", "USB_D_N", "CONN_USB pin2", "USB 2.0 差分 (规格合并名 TP_USB_D+ / D-)",
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    ("TP_CHG_STAT", "CHG_STAT", "R_PU_CHG_STAT", "充电状态",
     "BQ25896 STAT 脚 -> 回答 Q4b.4", "必装"),
    ("TP_PG", "PWR_GOOD", "R_PU_PG", "电源好 (BQ25896 PG 脚)", "充电板 -> 主 PCB 跨板点", "必装"),
    ("TP_ID", "ID_DETECT_0", "R_PU_ID0", "板级版本识别 (I2C EEPROM 或 GPIO 编码)",
     "主 PCB", "必装"),
    ("TP_LED_R", "LED_R", "R_LED_R", "LED 红", "主 PCB", "必装"),
    ("TP_LED_G", "LED_G", "R_LED_G", "LED 绿", "主 PCB", "必装"),
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    ("TP_KEY_VM", "KEY_VOL_M", "R_KEY_VM", "音量- 键", "主 PCB", "必装"),
    ("TP_RESET", "RESET_N", "R_PU_RESET_N", "复位网", "主 PCB", "必装"),
    ("TP_BOOT", "BOOT_N", "R_PU_BOOT_N", "BOOT 网", "主 PCB", "必装"),
    ("TP_JTAG", "JTAG_TCK", "J_DEBUG pin1", "JTAG 时钟", "调试排针", "必装"),
    ("TP_UART", "UART_TX", "J_UART pin1", "UART TX (与 USB 二选一)", "调试排针", "可选"),
]


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    add("P8", "GND", "SW_BOOT", "GND", "SW_BOOT", "BOOT 按键 (待选型)", "SW", "必装", "[推算]",
        "", "BOOT 键 -> GND", "B-11")
    # ---- JTAG 4 线 ----
    for sig, pin in (("JTAG_TCK", "pin1"), ("JTAG_TMS", "pin2"), ("JTAG_TDI", "pin3"),
                     ("JTAG_TDO", "pin4")):
        conn_row(by_id, "B-19", "P8", f"{sig}_SOC", f"SoC[TBD-01].{sig}", f"R_{sig}",
                 f"NET_{sig}_SOC")
        add("P8", sig, f"R_{sig}", f"J_DEBUG {pin}", f"R_{sig}", "100Ω ±1%", "R", "必装",
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        "CONN", "必装", "[推算]", "",
        "[J_DEBUG] JTAG 调试排针 (不装贴片, 手工可焊); pin1=TCK, 2=TMS, 3=TDI, 4=TDO")
    # ---- UART 2 线 (与 USB 二选一) ----
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
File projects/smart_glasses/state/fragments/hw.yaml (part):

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  waiting_on: boss
  due: '2026-10-31'
  item: 'ISS-067 待老板裁决: UVP 抬到 3.35V (方案A'') + 充电板 VSYS=NC (PM 10-26 裁决) => 电池低于 3.35V 时 3.3V 轨起不来, 插
    USB 也开不了机 (SYS 只来自电池), 只能先充电到 3.35V 再开机。选项: (a) 接受 (默认按我的假设继续: 先充电再开机, 不加铰链 pin); (b) 充电板 VSYS 接通
    (多 2 根铰链 pin, 触发结构接口变更); (c) UVP 降到 3.0V (必须走 buck-boost 方案 B, +1 IC +35mm2)。请老板/项目总工拍板'
- key: iss067_vendor_r_on_u1
  to: main
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  item: '★ISS-144 规格 §5 R11: onsemi 问询函 (ISS-142) 一封未发, 而它同时卡着 R2 (tuning) / R3 (CRA) / R4 (VDD_IO abs
    max) / R10 (fine exposure) 4 条 ⇒ ★它是本单最长的外部依赖。★请在放行 ISS-142 时把问询单补成 7+5 项: ①lane 速率与位深档位 (450MHz=10bit
    / 360MHz=8bit, 跟 pixclk 绑定) ②有没有现成 Rockchip ISP3 的 IQ 文件 ③fine exposure 寄存器是否存在 (S2 驱动只写了 coarse 0x3012)
    ④VDD_IO abs max (定 I2C 上拉 2.8V 还是 3.3V) ⑤完整 pinout 与电源域 (SENSOR_AVDD 2.8V 到底对应哪个脚)。★前 5 条正好对应规格的 C2/C3/C6/R4/R10,
    建议优先问 (due 11-03)。'
  since: '2026-11-02'
  waiting_on: agent
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  ref: HW/PCB/FET3576C_PIN_TABLE.csv
- key: carrier_board_en_power
  value: must_enable
  note: '★★★F13 新致命项 (与 F1 EN 悬空同级): **pin87 CARRIER_BOARD_EN (SOM 输出, 控制底板上电)** + **pin91~97 VCC_DCIN
    (5-13V)** ⇒ ★★**主板电源必须由 CARRIER_BOARD_EN 使能, 不得直连** —— Forlinx 原文警告: 底板早于核心板上电 ⇒ 通电瞬间电流过大/无法启动/**可能对处理器造成不可逆损坏**
    ⇒ ★**投板后才发现 = 板子起不来 ⇒ 已入 F1~F13 清单**。'
  ref: ISS-159 (F13) + ISS-162 段 B
- key: camera_module_power
  value: 3v3+5v_module_level
  note: '★★Radxa Camera 4K 31 针表: pin28/29=VCC3.3V, pin30/31=VCC5V ⇒ **模组级供电** ⇒ ★★主板的 SENSOR_CORE/SENSOR_VDD_IO/SENSOR_AVDD
    三条轨 + 三颗 TPS7A20 + 六个去耦位 **全部不需要** (模组内自稳压) ⇒ ★**推翻 11-02 19:5x 的"三轨按芯片 datasheet 重核"** ⇒ ★**教训: 选型先看模组接口表,
    再看芯片 datasheet**; 另: CSI **4-lane 必装** + 新增 CAM_RESET_N / CAM_PWDN / DSI_RESET_N 三个 net。'
  ref: HW/NETLIST_REV2_SPEC.md §0/§1 + HW/STEP1_PARTS_SPEC.md §2
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  note: '★公开依据: Forlinx OK3572-C 手册 §4 Hardware Design Guide/Power-on Sequence: 用 CARRIER_BOARD_EN 作为底板上电时序使能,
    否则 Excessive inrush current / Device failure to boot / In the worst-case scenario, irreversible damage
    to the processor; §3.5.1: SoM 启动后经该脚 3.3V(1k上拉) 放行 U3 出 VCC_5V; §3.5.1 Note: strictly adhere to the
    power-up sequencing。★网表已落(09:43:38版): J_SOM_P3 pin87→U_EN_SW EN→RAIL_BOARD_5V, SoM 侧 RAIL_SOM_DCIN
    直连 RAIL_DEMO_5V。★残留: U_EN_SW 无IC声明行(型号/Ron/电流未选) + SCHEMATIC_V1_SPEC.json 未同步 + 网表门禁缺每条RAIL_*必须有输出驱动的判据'
  ref: HW/STEP1_LANDING_LIST.md §3.1-F13; HW/PCB/FET3572C_PIN_TABLE.csv:287; state/_os_snapshots/fx3572_manual.html
    §4/§3.5.1
- key: iss159_f14_camera_module_power
  value: 主板不供 sensor 芯片级三条轨; camera 模组只要 pin28/29=3.3V 与 pin30/31=5V
  note: '★模组级 vs 芯片级: Radxa Camera 4K 31针表 pin28/29=VCC3.3V, pin30/31=VCC5V ⇒ 模组内部自己稳压 ⇒ 主板 SENSOR_CORE/SENSOR_VDD_IO/SENSOR_AVDD
    三轨 + 三颗 TPS7A20 + 六个去耦位全部 DNP。★教训: 芯片级电源参数≠模组级接口, 选型必须先看模组接口表再看芯片 datasheet'
  ref: HW/PCB/FPC_PIN_TABLES.md:20-21; HW/netlist_v1.csv:87-109; HW/SCHEMATIC_V1_SPEC.json power_rails
- key: iss159_f15_display_backlight_short
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
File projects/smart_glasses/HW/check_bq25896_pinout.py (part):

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    (12, ("QON",   "DI", {"QON", "NC"},
          "BATFET enable/reset control input. ... The pin contains an internal pull-up to maintain default high logic")),
    (13, ("BAT",   "P",  {"BAT_CHG", "BAT"},
          "Battery connection point to the positive terminal of the battery pack. ... Connect a 10uF closely to the BAT pin.")),
    (14, ("BAT",   "P",  {"BAT_CHG", "BAT"},
          "Battery connection point to the positive terminal of the battery pack. ... Connect a 10uF closely to the BAT pin.")),
    (15, ("SYS",   "P",  {"SYS_CHG", "SYS"},
          "System connection point. ... Connect a 20uF closely to the SYS pin.")),
    (16, ("SYS",   "P",  {"SYS_CHG", "SYS"},
          "System connection point. ... Connect a 20uF closely to the SYS pin.")),
    (17, ("PGND",  "P",  {"PGND", "GND", "TS_RTN"},
          "Power ground connection for high-current power converter node. ... A single point connection is recommended ...")),
    (18, ("PGND",  "P",  {"PGND", "GND", "TS_RTN"},
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          "Switching node connecting to output inductor. ... Connect the 0.047uF bootstrap capacitor from SW to BTST.")),
    (21, ("BTST",  "P",  {"BTST"},
          "PWM high side driver positive supply. ... Connect the 0.047uF bootstrap capacitor from SW to BTST.")),
    # ★★2026-11-02 02:1x 收紧: 原允许集合含 TS_BAT ⇒ 一处笔误 (RT1 的 TS 端写成 "U_CHG pin22"
    #   而不是 pin11) 被放过 ⇒ TS 与 REGN 短接 (BQ25896 内部 5V LDO 输出被短到电池 NTC 节点)。
    #   **REGN 是 LDO 输出, 只能是 REGN / REGN_5V** —— TS 归 pin11。
    (22, ("REGN",  "P",  {"REGN", "REGN_5V"},
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                m = JCHG_RE.search(r.get(side) or "")
                if m:
                    jmap[int(m.group(1))].add(r.get("net", ""))
    # 规格 §5.2 提案表: | pin5 | `TS_BAT` | ... | pin6 | `CHG_STAT` | ... | pin7 | `PWR_GOOD` |
    #                   pin8 | `VBUS_DET` | pin9 | `I2C_CHG_SCL` | pin10 | `I2C_CHG_SDA` |
    # ★★2026-11-02 03:0x 更新: 原快照是**过期**的 —— V1.8 把 TS_BAT 从 pin5 挪到 pin8
    #   (pin5 改给 CHG_STAT), 于是 CHG_STAT/PWR_GOOD/VBUS_DET 各前移一位;
    #   pin9/pin10 的 BQ25896-I2C 跨铰链方案**未采用** (见 CHARGE_BOARD_SPEC.md §5.3
    #   "若要据此调充电电流, 就需要 BQ25896 的 I2C 跨铰链" —— 本轮不做) ⇒ pin9 = 预留 HINGE_RSV, pin10 = TS 专用回流。
    #   ⇒ 现在的网表是**新的**、这份快照是**旧的** ⇒ 本条判据应当跟网表对齐, 并把差异登记进 CHARGE_BOARD_SPEC.md §5。
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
